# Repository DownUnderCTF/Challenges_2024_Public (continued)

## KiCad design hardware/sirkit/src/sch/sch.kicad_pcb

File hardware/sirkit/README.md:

sirkit
======================

- **Category**: hardware
- **Difficulty**: hard
- **Author**: HexF
- **Tags**: 

We intercepted some design files. Maybe you can make sense of them?

---

### Handout files

- [./publish/sirkit.tar](./publish/sirkit.tar)

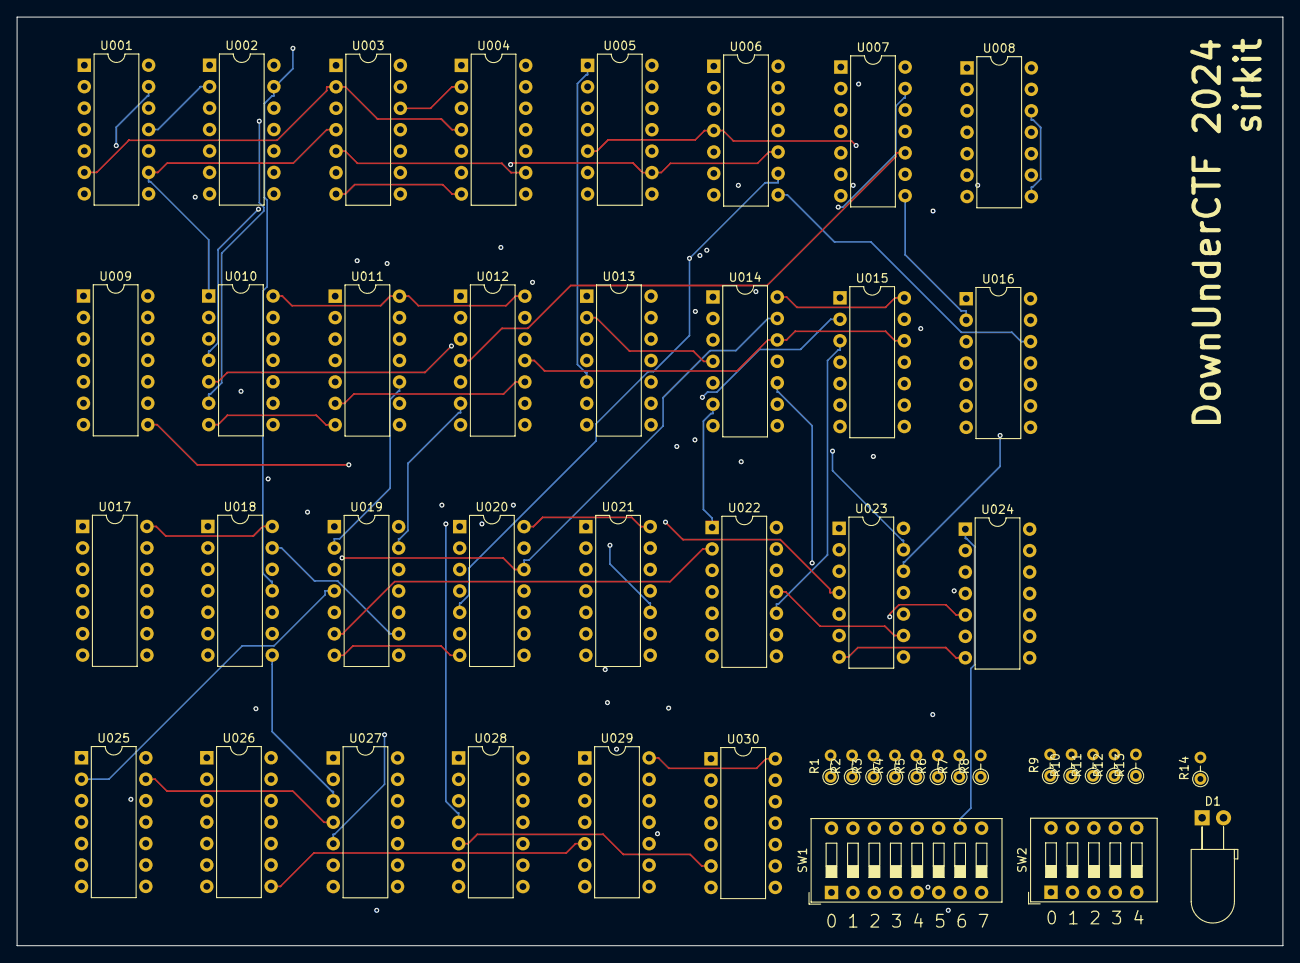
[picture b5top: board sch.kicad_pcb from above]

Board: 4 copper layers, 149.9 x 110.0 mm, 47 parts (0 on the bottom side), 104 nets.

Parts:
D1: LED_D5.0mm_Horizontal_O3.81mm_Z15.0mm
R1, R2, R3, R4, R5, R6, R7, R8, R9, R10, R11, R12, R13, R14: R_Axial_DIN0204_L3.6mm_D1.6mm_P2.54mm_Vertical
SW1: SW_DIP_SPSTx08_Slide_9.78x22.5mm_W7.62mm_P2.54mm
SW2: SW_DIP_SPSTx05_Slide_9.78x14.88mm_W7.62mm_P2.54mm
U001, U028: 74LS04; DIP-14_W7.62mm
U002, U007, U018, U027: 74LS02; DIP-14_W7.62mm
U003, U004, U006, U009, U011, U013, U014, U016, U017, U019, U020, U021, U023, U026, U030: 74LS40; DIP-14_W7.62mm
U005, U008, U012, U025: 74LS00; DIP-14_W7.62mm
U010, U015, U022: 74LS08; DIP-14_W7.62mm
U024, U029: 74LS86; DIP-14_W7.62mm

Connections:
$abc$1463$new_n15.0: U001.2, U003.13, U004.1, U005.10, U006.1, U006.13, U013.1, U013.13, U017.13, U026.1
$abc$1463$new_n16.0: U001.4, U002.6, U004.13, U006.2, U011.1
$abc$1463$new_n17.0: U001.6, U003.2, U004.4, U007.9, U011.2, U011.12
$abc$1463$new_n18.0: U001.8, U002.3, U005.13, U006.12, U011.10, U013.12, U017.10, U019.2, U023.4
$abc$1463$new_n19.0: U001.10, U003.5, U004.9, U007.5, U011.5, U011.9, U013.4, U013.10, U014.5, U017.9, U020.4
$abc$1463$new_n20.0: U001.12, U029.1
$abc$1463$new_n21.0: U002.1, U006.5, U016.5
$abc$1463$new_n22.0: U002.4, U006.9, U020.5
$abc$1463$new_n23.0: U003.6, U010.4
$abc$1463$new_n24.0: U002.10, U005.1, U008.10, U013.5, U019.5, U028.1
$abc$1463$new_n25.0: U013.9, U026.2, U028.2
$abc$1463$new_n26.0: U004.5, U005.2, U010.3
$abc$1463$new_n27.0: U005.3, U010.5
$abc$1463$new_n28.0: U002.12, U010.6
$abc$1463$new_n29.0: U002.13, U007.11, U018.11
$abc$1463$new_n30.0: U007.1, U008.2, U009.9, U026.4, U028.3
$abc$1463$new_n31.0: U003.9, U028.4
$abc$1463$new_n32.0: U005.6, U026.5
$abc$1463$new_n33.0: U003.8, U009.1
$abc$1463$new_n34.0: U005.12, U007.4, U023.5
$abc$1463$new_n35.0: U005.8, U012.1
$abc$1463$new_n36.0: U004.6, U009.2, U017.1, U023.13
$abc$1463$new_n37.0: U007.10, U012.4
$abc$1463$new_n38.0: U004.8, U015.1
$abc$1463$new_n39.0: U006.6, U009.4, U016.13, U021.13
$abc$1463$new_n40.0: U005.11, U008.4
$abc$1463$new_n41.0: U006.8, U009.5, U016.12, U021.12
$abc$1463$new_n42.0: U007.12, U009.6
$abc$1463$new_n43.0: U007.13, U008.13, U010.10, U026.13
$abc$1463$new_n44.0: U008.3, U008.5, U012.2
$abc$1463$new_n45.0: U008.6, U008.9
$abc$1463$new_n46.0: U008.8, U008.12, U010.9, U017.2, U023.12
$abc$1463$new_n47.0: U010.8, U020.13, U021.1
$abc$1463$new_n48.0: U008.11, U018.3
$abc$1463$new_n49.0: U012.3, U012.5
$abc$1463$new_n50.0: U010.13, U012.6, U015.13, U019.13, U021.10, U022.13
$abc$1463$new_n51.0: U009.8, U010.12, U021.2
$abc$1463$new_n52.0: U010.11, U014.13, U020.12
$abc$1463$new_n53.0: U011.6, U012.10, U019.12
$abc$1463$new_n54.0: U011.8, U015.2
$abc$1463$new_n55.0: U012.9, U015.3, U022.10
$abc$1463$new_n56.0: U012.8, U012.12
$abc$1463$new_n57.0: U012.11, U014.12, U015.12, U021.4
$abc$1463$new_n58.0: U013.6, U014.10, U023.10, U025.4
$abc$1463$new_n59.0: U013.8, U015.10, U016.10
$abc$1463$new_n60.0: U014.6, U015.4, U022.1, U025.10
$abc$1463$new_n61.0: U015.5, U021.9, U022.4, U025.3, U025.5
$abc$1463$new_n62.0: U015.6, U015.9
$abc$1463$new_n63.0: U014.9, U015.8
$abc$1463$new_n64.0: U014.8, U018.2
$abc$1463$new_n65.0: U018.1, U018.8, U027.3
$abc$1463$new_n66.0: U015.11, U017.4, U026.12
$abc$1463$new_n67.0: U016.6, U016.9
$abc$1463$new_n68.0: U018.6, U025.6
$abc$1463$new_n69.0: U016.8, U018.5
$abc$1463$new_n70.0: U017.5, U018.4
$abc$1463$new_n71.0: U017.6, U018.9
$abc$1463$new_n72.0: U018.10, U024.2
$abc$1463$new_n73.0: U024.3, U030.1
$abc$1463$new_n74.0: U017.8, U019.10, U020.10
$abc$1463$new_n75.0: U019.6, U022.2, U025.9, U026.10
$abc$1463$new_n76.0: U021.5, U022.3
$abc$1463$new_n77.0: U018.12, U025.8
$abc$1463$new_n78.0: U018.13, U019.9
$abc$1463$new_n79.0: U019.8, U027.2
$abc$1463$new_n80.0: U027.1, U029.9
$abc$1463$new_n81.0: U020.6, U022.5
$abc$1463$new_n82.0: U020.9, U022.6
$abc$1463$new_n83.0: U020.8, U024.5
$abc$1463$new_n84.0: U024.6, U027.11
$abc$1463$new_n85.0: U021.6, U024.9
$abc$1463$new_n86.0: U024.8, U027.8
$abc$1463$new_n87.0: U021.8, U024.12
$abc$1463$new_n88.0: U022.9, U023.6
$abc$1463$new_n89.0: U022.8, U022.12
$abc$1463$new_n90.0: U022.11, U023.9
$abc$1463$new_n91.0: U023.8, U029.2
$abc$1463$new_n92.0: U024.11, U027.5
$abc$1463$new_n93.0: U025.13, U027.4
$abc$1463$new_n94.0: U025.12, U029.3
$abc$1463$new_n95.0: U025.11, U027.9
$abc$1463$new_n96.0: U027.10, U030.2
$abc$1463$new_n97.0: U026.6, U026.9
$abc$1463$new_n98.0: U026.8, U029.5
$abc$1463$new_n99.0: U027.12, U029.6
$abc$1463$new_n100.0: U029.8, U030.4
$abc$1463$new_n101.0: U027.13, U030.5
$abc$1463$new_n102.0: U028.5, U030.6
GND: D1.2, SW1.1, SW1.2, SW1.3, SW1.4, SW1.5, SW1.6, SW1.7, SW1.8, U001.7, U002.7, U003.7, U004.7, U005.7, U006.7, U007.7, U008.7, U009.7, U010.7, U011.7, U012.7, U013.7, U014.7, U015.7, U016.7, U017.7, U018.7, U019.7, U020.7, U021.7, U022.7, U023.7, U024.7, U025.7, U026.7, U027.7, U028.7, U029.7, U030.7
VCC: R1.2, R2.2, R3.2, R4.2, R5.2, R6.2, R7.2, R8.2, R9.2, R10.2, R11.2, R12.2, R13.2, U001.14, U002.14, U003.14, U004.14, U005.14, U006.14, U007.14, U008.14, U009.14, U010.14, U011.14, U012.14, U013.14, U014.14, U015.14, U016.14, U017.14, U018.14, U019.14, U020.14, U021.14, U022.14, U023.14, U024.14, U025.14, U026.14, U027.14, U028.14, U029.14, U030.14
byte_guess.0: R1.1, R2.1, R3.1, R4.1, R5.1, R6.1, R7.1, R8.1, SW1.16, U029.4
byte_guess.1: SW1.15, U001.13
byte_guess.2: SW1.14, U029.10
byte_guess.3: SW1.13, U024.13
byte_guess.4: SW1.12, U024.4
byte_guess.5: SW1.11, U024.10
byte_guess.6: SW1.10, U024.1
byte_guess.7: SW1.9, U027.6
byte_num.0: R9.1, R10.1, R11.1, R12.1, R13.1, SW2.10, U001.5, U002.5, U002.9, U003.10, U004.12, U005.5, U006.4, U009.10, U016.4, U017.12, U023.2
byte_num.1: SW2.9, U001.3, U002.8, U003.1, U003.12, U004.2, U005.4, U007.8, U009.12, U011.13, U014.2, U016.2, U023.1
byte_num.2: SW2.8, U001.9, U003.4, U004.10, U007.3, U010.1, U011.4, U013.2, U014.4, U020.2
byte_num.3: SW2.7, U001.11, U002.2, U005.9, U006.10, U007.2, U010.2, U019.4, U025.2
byte_num.4: SW2.6, U001.1, U002.11, U007.6, U008.1, U009.13, U012.13, U014.1, U016.1, U019.1, U020.1, U025.1
guess_valid.0: R14.2, U028.6

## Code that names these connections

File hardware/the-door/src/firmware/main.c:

#include <stdbool.h>
#include <string.h>
#include "pico/stdlib.h"
#include "pico/rand.h"
#include "bbspi.h"

#define PIN_WDAT 10
#define PIN_RCLK 11
#define PIN_WCLK 12

#define PIN_FLAG_RELEASE 13

static bool release_flag = false;

size_t bbspi_handle_new_cmd(const uint8_t cmd, uint8_t *tx_data)
{
    uint8_t challenge_info[] = {
        0x43, 0x46, 0x43, 0x31,  // CFC1
        0x00, 0x00, 0x00, 0x00,  // no serial
        0x00, 0x00, 0x00, 0x02,  // chal id
        0xa0, 0x1c, 0x79, 0xdd}; // crc32
    if (cmd == 0x03)
    {
        // wait for addr then tx info
        memcpy(tx_data + 3, challenge_info, sizeof(challenge_info));
        release_flag = false;
    }
    else if (cmd == 0x0F) // Flag release command
    {
        tx_data[0] = release_flag ? 0x81 : 0x80; // not 0 so we can test RX is working too - last bit represents flag release
    }
}

void shift_bit(bool bit)
{
    gpio_put(PIN_WDAT, bit);

    // 'clock'
    gpio_put(PIN_WCLK, true);
    gpio_put(PIN_RCLK, false);
    sleep_ms(64);
    gpio_put(PIN_WCLK, false);
    gpio_put(PIN_RCLK, true);
    sleep_ms(64);

    gpio_put(PIN_RCLK, false);
}

void shift_u32(uint32_t n)
{
    for (size_t i = 0; i < 32; i++)
    {
        shift_bit(n & 1);
        n >>= 1;
    }
}

void bbspi_gpio_callback_passthrough(uint16_t gpio, uint16_t events)
{
    if (gpio == PIN_FLAG_RELEASE && events & (GPIO_IRQ_EDGE_FALL | GPIO_IRQ_EDGE_RISE))
    {
        // somehow flag release changed - good enough for a release!
        release_flag = true;
    }
}

int main()
{
    stdio_init_all();

    gpio_init(PIN_WDAT);
    gpio_init(PIN_RCLK);
    gpio_init(PIN_WCLK);
    gpio_init(PIN_FLAG_RELEASE);

    gpio_set_dir(PIN_WDAT, GPIO_OUT);
    gpio_set_dir(PIN_RCLK, GPIO_OUT);
    gpio_set_dir(PIN_WCLK, GPIO_OUT);

    gpio_set_dir(PIN_FLAG_RELEASE, GPIO_IN);

    shift_u32(0b00011000000000000000000000000000); // a debrujin will catch this trivially, guessing, not so much

    gpio_set_irq_enabled(PIN_FLAG_RELEASE, GPIO_IRQ_EDGE_FALL | GPIO_IRQ_EDGE_RISE, true);

    bbspi_init(5, 6, 4, 3);

    while (1)
    {
    }
}

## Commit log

2024-07-07 DUCTF 2024 challenges
2024-07-08 hardware/ductf: publish writeup and src
2024-07-09 beginner/parrot-the-emu: fix underscores in writeup
